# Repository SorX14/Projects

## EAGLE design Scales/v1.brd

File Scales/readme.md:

# Arduino Scales

More information available [here](http://www.s-parker.uk/2014/10/hacking-bathroom-scales-with-an-arduino-the-easy-way/).

## Theory

The idea was to modify existing bathroom scales to output its result to the internet. The scales themselves should still work as before. 

## PCB

The PCB uses an XRF radio, along with a MCP3421 18bit ADC, the Wheatstone bridge made up of 4 strain gauges can be measured accurately (~90g per step).

A single gate 74AHC inverter takes the LCD backlight signal and uses it to wake the Atmega328 chip from deep sleep.

## Parts list

- Various 0805 resistors and capacitors
- **SMD crystal** - 16 Mhz TXC 7B-16.000MAAJ-T - Farnell no: 1841977
- **ATMEGA328P-AU** - TQFP-32 package - Farnell no: 1715486
- **Microchip MCP3421A1T-E/CH** - Farnell no: 1605568
- **NXP 74AHC1G04GW/T1** - Single gate SOT-353 inverter - Farnell no: 1085239
- **TI TPS73133DBVTG4** - 0.15A 3.3v voltage regulator - Farnell no: 1207341

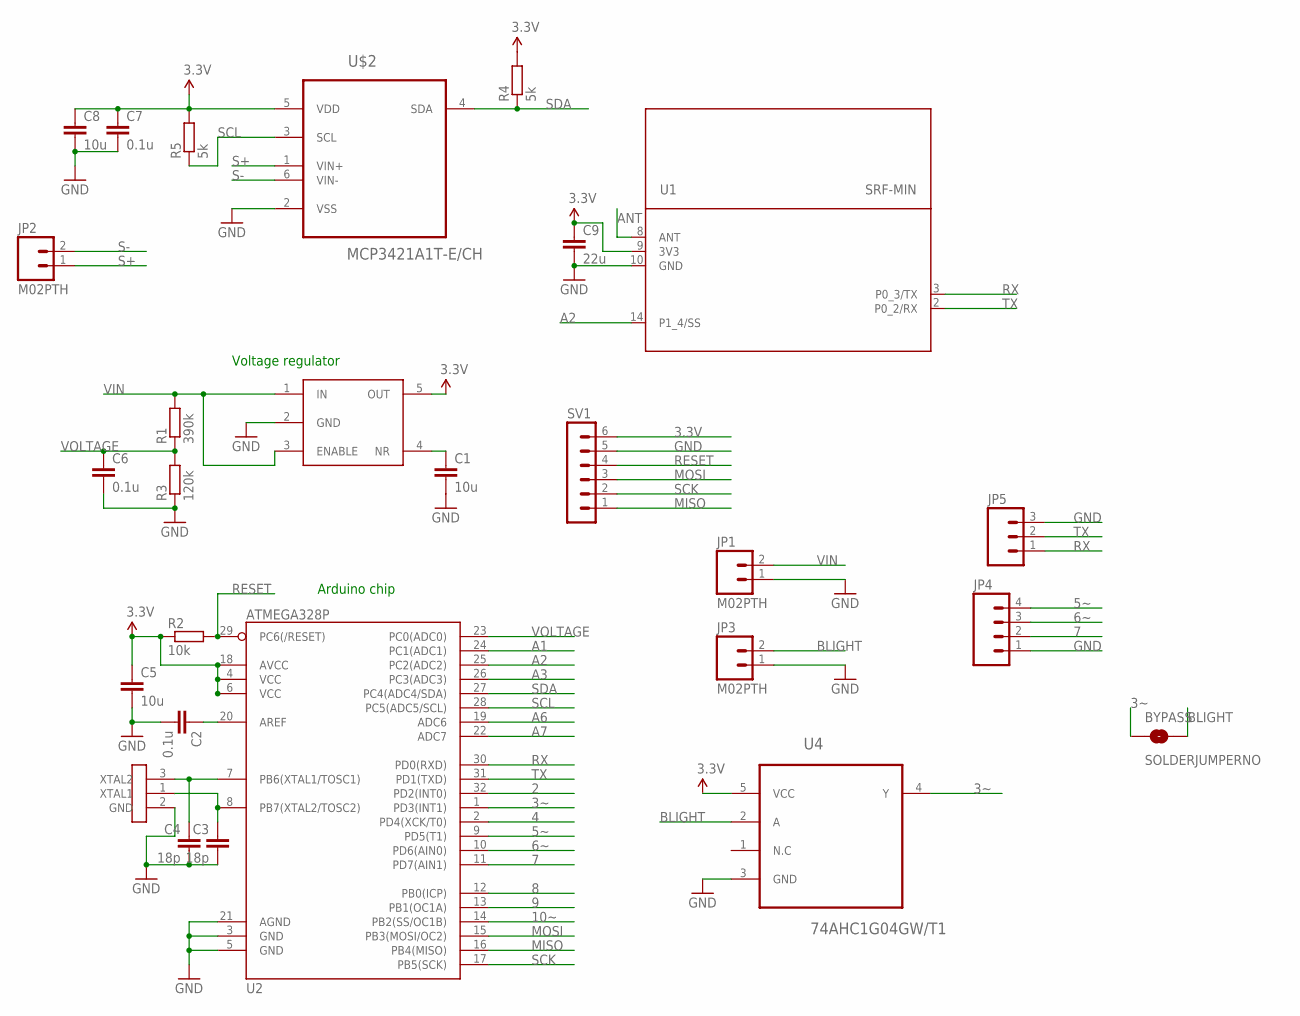
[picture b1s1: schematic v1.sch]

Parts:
BYPASS: SOLDERJUMPERNO; SJ_2S-NO
C1, C5, C8: 10u; C0805
C2, C6, C7: 0.1u; C0805
C3, C4: 18p; C0805
C9: 22u; C0805
JP1, JP2, JP3: M02PTH; 1X02
JP4: M04PTH; 1X04
JP5: M03PTH; 1X03
R1: 390k; R0805
R2: 10k; R0805
R3: 120k; R0805
R4, R5: 5k; R0805
SV1: MA06-1
TPS73133: TPS731XX; SOT95P284X120-5N
U1: SRF-MIN; SRF-LANDING-1.2-MIN
U2: ATMEGA328P; TQFP32-08
U4: 74AHC1G04GW/T1; SOT65P210X110-5N
U$1: CRYSTAL-GND; CRYSTAL-SMD-5X3-LARGE-GND
U$2: MCP3421A1T-E/CH; SOT95P270X145-6N

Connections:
2: U2.32 (PD2(INT0))
3.3V: C5.1, C7.1, C8.1, C9.1, R2.1, R4.2, R5.2, SV1.6, TPS73133.5 (OUT), U1.9 (3V3), U2.4 (VCC), U2.6 (VCC), U2.18 (AVCC), U4.5 (VCC), U$2.5 (VDD)
3~: BYPASS.1, U2.1 (PD3(INT1)), U4.4 (Y)
4: U2.2 (PD4(XCK/T0))
5~: JP4.4, U2.9 (PD5(T1))
6~: JP4.3, U2.10 (PD6(AIN0))
7: JP4.2, U2.11 (PD7(AIN1))
8: U2.12 (PB0(ICP))
9: U2.13 (PB1(OC1A))
10~: U2.14 (PB2(SS/OC1B))
A1: U2.24 (PC1(ADC1))
A2: U1.14 (P1_4/SS), U2.25 (PC2(ADC2))
A3: U2.26 (PC3(ADC3))
A6: U2.19 (ADC6)
A7: U2.22 (ADC7)
ANT: U1.8 (ANT)
BLIGHT: BYPASS.2, JP3.2, U4.2 (A)
GND: C1.2, C2.2, C3.2, C4.2, C5.2, C6.2, C7.2, C8.2, C9.2, JP1.1, JP3.1, JP4.1, JP5.3, R3.1, SV1.5, TPS73133.2 (GND), U1.10 (GND), U2.3 (GND), U2.5 (GND), U2.21 (AGND), U4.3 (GND), U$1.2 (GND), U$2.2 (VSS)
MISO: SV1.1, U2.16 (PB4(MISO))
MOSI: SV1.3, U2.15 (PB3(MOSI/OC2))
unnamed: C2.1, U2.20 (AREF)
unnamed: C4.1, U2.7 (PB6(XTAL1/TOSC1)), U$1.3 (XTAL2)
unnamed: C3.1, U2.8 (PB7(XTAL2/TOSC2)), U$1.1 (XTAL1)
unnamed: C1.1, TPS73133.4 (NR)
RESET: R2.2, SV1.4, U2.29 (PC6(/RESET))
RX: JP5.1, U1.3 (P0_3/TX), U2.30 (PD0(RXD))
S+: JP2.1, U$2.1 (VIN+)
S-: JP2.2, U$2.6 (VIN-)
SCK: SV1.2, U2.17 (PB5(SCK))
SCL: R5.1, U2.28 (PC5(ADC5/SCL)), U$2.3 (SCL)
SDA: R4.1, U2.27 (PC4(ADC4/SDA)), U$2.4 (SDA)
TX: JP5.2, U1.2 (P0_2/RX), U2.31 (PD1(TXD))
VIN: JP1.2, R1.2, TPS73133.1 (IN), TPS73133.3 (ENABLE)
VOLTAGE: C6.1, R1.1, R3.2, U2.23 (PC0(ADC0))

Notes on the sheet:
Voltage regulator
Arduino chip

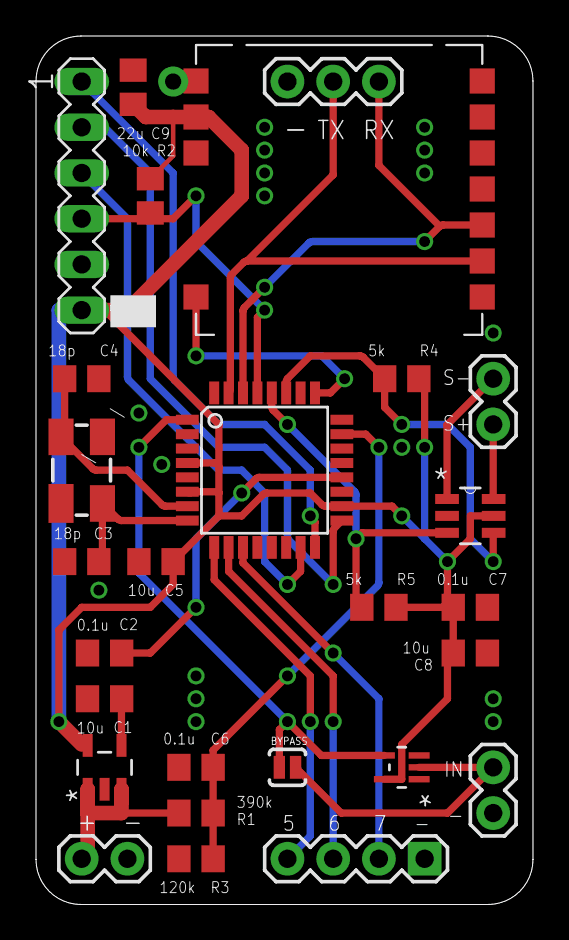
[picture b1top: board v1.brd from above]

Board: 2 copper layers, 27.6 x 48.2 mm, 27 parts (0 on the bottom side), 24 nets.

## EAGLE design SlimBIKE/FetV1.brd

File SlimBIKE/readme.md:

Arduino bike lights
===

Documentation and build log available [here](http://www.s-parker.uk/2014/08/making-arduino-bike-lights/).

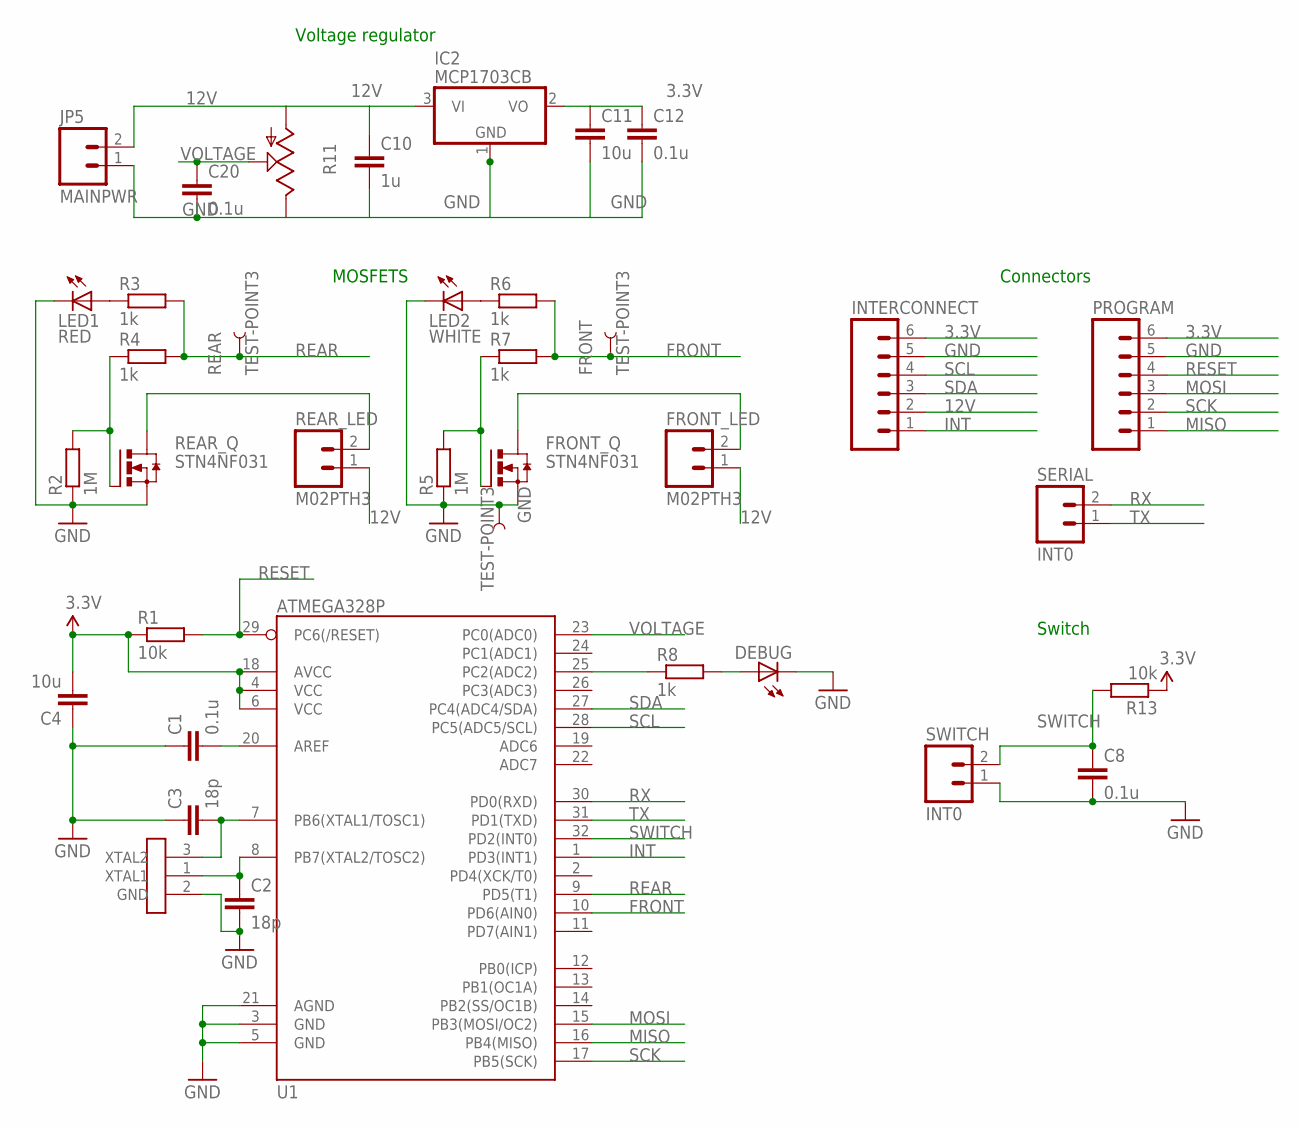
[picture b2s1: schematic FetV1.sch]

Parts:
C1, C8, C12, C20: 0.1u; C0805
C2, C3: 18p; C0805
C4, C11: 10u; C0805
C10: 1u; C0805
DEBUG: LEDSML0805; SML0805
FRONT: TEST-POINT3; PAD.03X.03
FRONT_LED: M02PTH3; 1X02_LONGPADS
FRONT_Q: STN4NF031; SOT223
GND: TEST-POINT3; PAD.03X.03
IC2: MCP1703CB; SOT23
INTERCONNECT: M06SIP; 1X06
JP5: MAINPWR; 1X02_LONGPADS
LED1: RED; SML0805
LED2: WHITE; SML0805
PROGRAM: M06SIP; 1X06
R1, R13: 10k; R0805
R2, R5: 1M; R0805
R3, R4, R6, R7, R8: 1k; R0805
R11: TRIM_US-B64W; B64W
REAR: TEST-POINT3; PAD.03X.03
REAR_LED: M02PTH3; 1X02_LONGPADS
REAR_Q: STN4NF031; SOT223
SERIAL: INT0; 1X02
SWITCH: INT0; 1X02_LONGPADS
U1: ATMEGA328P; TQFP32-08
U$1: CRYSTAL-GND; CRYSTAL-SMD-5X3-LARGE-GND

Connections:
3.3V: C4.2, C11.1, C12.1, IC2.2 (VO), INTERCONNECT.6, PROGRAM.6, R1.1, R13.1, U1.4 (VCC), U1.6 (VCC), U1.18 (AVCC)
12V: C10.1, FRONT_LED.1, IC2.3 (VI), INTERCONNECT.2, JP5.2, R11.A, REAR_LED.1
FRONT: FRONT.P$1, R6.2, R7.2, U1.10 (PD6(AIN0))
GND: C1.1, C2.2, C3.1, C4.1, C8.2, C10.2, C11.2, C12.2, C20.2, DEBUG.C, FRONT_Q.3 (S), GND.P$1, IC2.1 (GND), INTERCONNECT.5, JP5.1, LED1.C, LED2.C, PROGRAM.5, R2.1, R5.1, R11.E, REAR_Q.3 (S), SWITCH.1, U1.3 (GND), U1.5 (GND), U1.21 (AGND), U$1.2 (GND)
INT: INTERCONNECT.1, U1.1 (PD3(INT1))
MISO: PROGRAM.1, U1.16 (PB4(MISO))
MOSI: PROGRAM.3, U1.15 (PB3(MOSI/OC2))
unnamed: C3.2, U1.7 (PB6(XTAL1/TOSC1)), U$1.3 (XTAL2)
unnamed: C2.1, U1.8 (PB7(XTAL2/TOSC2)), U$1.1 (XTAL1)
unnamed: DEBUG.A, R8.2
unnamed: C1.2, U1.20 (AREF)
unnamed: REAR_LED.2, REAR_Q.2 (D), REAR_Q.4 (D)
unnamed: R2.2, R4.1, REAR_Q.1 (G)
unnamed: FRONT_LED.2, FRONT_Q.2 (D), FRONT_Q.4 (D)
unnamed: LED1.A, R3.1
unnamed: FRONT_Q.1 (G), R5.2, R7.1
unnamed: LED2.A, R6.1
unnamed: R8.1, U1.25 (PC2(ADC2))
REAR: R3.2, R4.2, REAR.P$1, U1.9 (PD5(T1))
RESET: PROGRAM.4, R1.2, U1.29 (PC6(/RESET))
RX: SERIAL.2, U1.30 (PD0(RXD))
SCK: PROGRAM.2, U1.17 (PB5(SCK))
SCL: INTERCONNECT.4, U1.28 (PC5(ADC5/SCL))
SDA: INTERCONNECT.3, U1.27 (PC4(ADC4/SDA))
SWITCH: C8.1, R13.2, SWITCH.2, U1.32 (PD2(INT0))
TX: SERIAL.1, U1.31 (PD1(TXD))
VOLTAGE: C20.1, R11.S, U1.23 (PC0(ADC0))

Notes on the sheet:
Voltage regulator
MOSFETS
Connectors
Switch

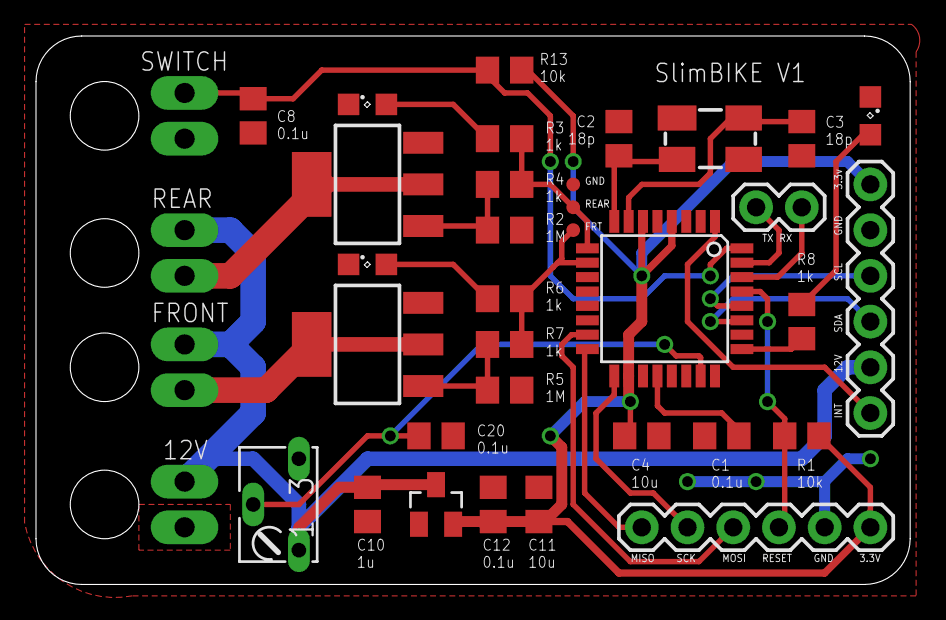
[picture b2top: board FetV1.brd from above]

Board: 2 copper layers, 48.6 x 30.5 mm, 37 parts (0 on the bottom side), 27 nets.

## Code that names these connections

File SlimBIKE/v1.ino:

#include <MsTimer2.h>
#include "LowPower.h"

// Pin definitions
#define REAR 5
#define FRONT 6
#define VOLTAGE A0
#define SWITCH 2
#define DEBUG 16

#define HOLD_TIME 2000

// Variables
volatile int state = 0; // The state of the device, wake, sleep, flash modes
volatile boolean blinker = false; // Control for flashing LED's
volatile unsigned long press_time = 0; // The press time of the switch
int button_value = 0; // The switch value
volatile int pressed_flag = 0; // A flag thats set when an interrupt is detected
unsigned long difference = 0; // The difference between first press and when its let go

void setup() {
  Serial.begin(115200);
  
  // Setup basic pins
  pinMode(FRONT, OUTPUT);
  pinMode(REAR, OUTPUT);
  pinMode(DEBUG, OUTPUT);
  pinMode(VOLTAGE, INPUT);
  pinMode(SWITCH, INPUT);
  
  // Setup analog reference
  analogReference(INTERNAL);
  
  // Setup the timer
  MsTimer2::set(150, FLASH);
 
  // Turn on the debug LED as we'll be on
  digitalWrite(DEBUG, HIGH);
  Serial.println("STARTING...");
  fadeBoth();

  // Start after we've done the fade
  MsTimer2::start();  
     
  // Attach the interrupts
  attachInterrupt(0, SWITCH_INT, FALLING);
}

void FLASH() {
  if (state == 1) {
    analogWrite(FRONT, 150);
    if (!blinker) {
      analogWrite(REAR, 100);
    } else {
      digitalWrite(REAR, LOW);
    }
  } else if (state == 2) {
    digitalWrite(FRONT, HIGH);
    digitalWrite(REAR, blinker);
  } else {
    digitalWrite(FRONT, LOW);
    digitalWrite(REAR, LOW);
  }
  blinker = !blinker;
}

void SWITCH_INT() {
  press_time = millis();
  pressed_flag = 1;
  
  state++;
  if (state > 2) {
    state = 0;
  }
}

void loop() { 
  button_value = digitalRead(SWITCH);

  // If we've just pressed the button
  if (pressed_flag == 1) {
    // If the button has stopped being pressed
    if (button_value == HIGH) {
      pressed_flag = 0;
    } else { // If the button is still being held
      difference = millis() - press_time;
      if (difference > HOLD_TIME) {
        // We're counting this as the button being pressed
        pressed_flag = 0;
        
        // Disable the button, the flashing, show voltage, then reenable everything
        detachInterrupt(0);
        MsTimer2::stop();
        showVoltage();
        state = 0; // Turn off after this
        MsTimer2::start();
        attachInterrupt(0, SWITCH_INT, FALLING);
      }
    }
  }

  // Flush the serial before the next loop, we get corruption otherwise
  if (state == 0 && pressed_flag == 0) {
    digitalWrite(FRONT, LOW);
    digitalWrite(REAR, LOW);
    
    Serial.flush();
    
    // Sleep until an interrupt
    digitalWrite(DEBUG, LOW); // Turn off the debug LED as we're going to sleep
    LowPower.powerDown(SLEEP_FOREVER, ADC_OFF, BOD_OFF);
    digitalWrite(DEBUG, HIGH); // Turn on the debug LED as we're awake
  }
}

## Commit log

2014-08-06 :space_invader: Added .gitattributes & .gitignore files
2014-08-06 Adding files
2014-08-06 Added readme
2014-08-06 Testing MD
2014-08-08 Home update
2014-08-08 Updated to reuse cookies
2014-08-08 Added more page IDs
2014-08-08 Updating documentation
2014-08-09 Added additional function to retrieve version data
2014-08-09 Updated for new function to retrieve version/update date
2014-08-09 Updated documentation and usage figures in multiple formats
2014-08-23 Adding SlimBIKE
2014-08-24 Adding PCBs and schematic image
2014-09-21 Adding IMU
2014-11-01 Adding scales eagle files and schematic
2014-11-02 Adding documentation
2014-11-02 Forgot the link
2014-11-04 Adding arduino sketch
2014-12-30 Forgot about these...
2015-08-13 Updated for new version
2015-08-13 Updating readme
2016-09-19 Add new function to return the up and down connection rate.
2016-11-23 Trim whitespace from data usage metrics
    When the data usage metrics are smaller numbers, the page
    may contain whitespace to the left of the number. This
    patch simply trims the whitespace from the left of the
    number before exploding it so that the returned data is
    more accurate.
2016-11-23 Add function to find noise margin
    This commit adds a function to fetch the noise margin data.
2016-11-23 Correct verbiage for function comments
    Some of the comments are incorrect - fix them.
2016-11-23 Add functions for line & signal attenuation
    Add new functions to fetch line and signal attenuation figures.

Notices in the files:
parts and their libraries:
SparkFun-FreqCtrl: Licensing: CC v3.0 Share-Alike You are welcome to use this library for commercial purposes.
